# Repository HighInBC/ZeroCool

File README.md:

# ZeroCool
Zero cool is a Raspberry Pi Zero based portable bitcoin wallet printer.

This project is not ready for public consumption at this point.

The name of the project is a reference to one of the best/worst hacker movies ever made **Hackers**(1995).

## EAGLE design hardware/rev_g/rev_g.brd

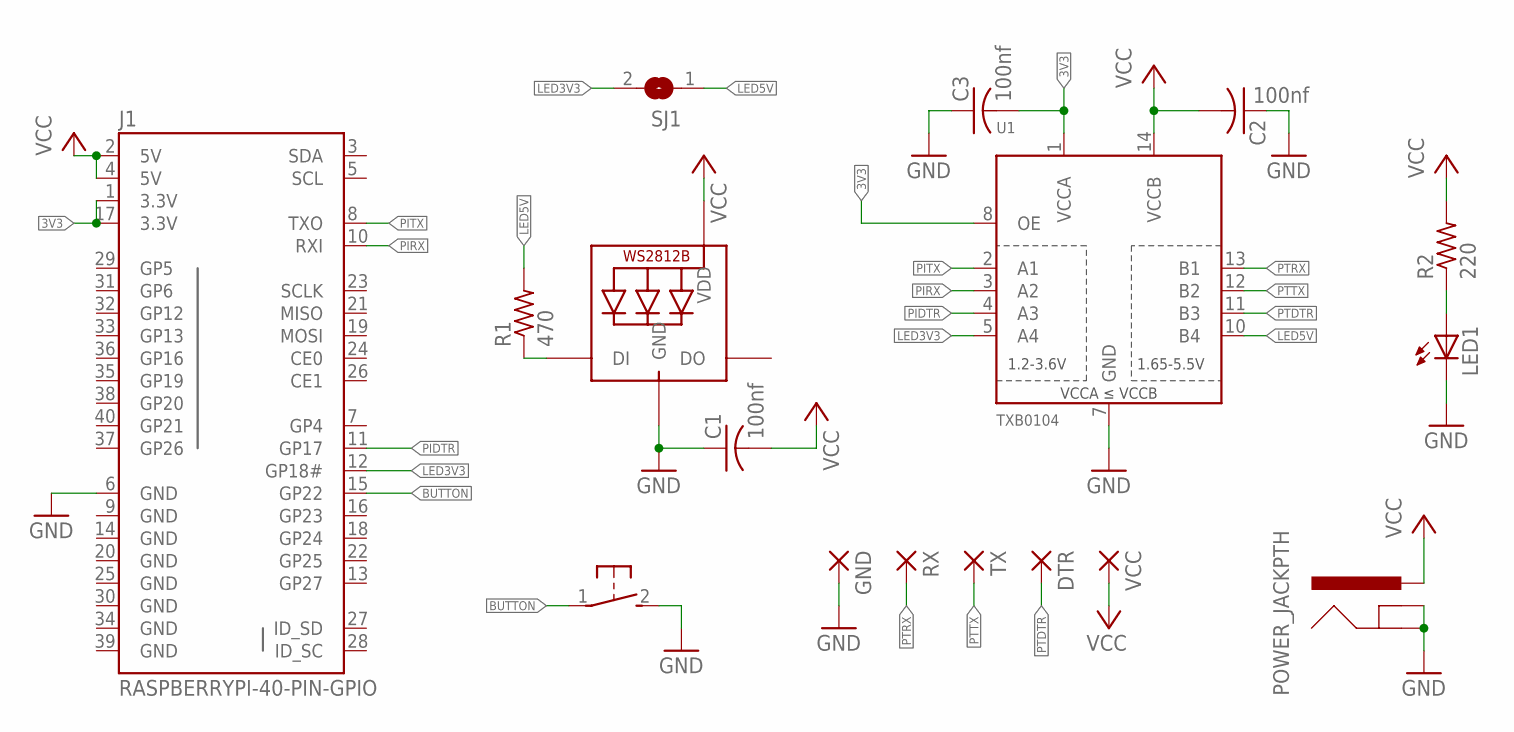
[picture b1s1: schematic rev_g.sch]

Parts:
C1, C2, C3: 100nf; C0805K
DTR: SMD5; SMD2,54-5,08
GND: SMD5; SMD2,54-5,08
J1: RASPBERRYPI-40-PIN-GPIO; 2X20-SHROUDED
J3: POWER_JACKPTH; POWER_JACK_PTH
LED1: LEDCHIPLED_0805; CHIPLED_0805
LED2: WS2812B5050; WS2812B
R1: 470; M0805
R2: 220; M0805
RX: SMD5; SMD2,54-5,08
S1: DTSM-3
SJ1: SJ
TX: SMD5; SMD2,54-5,08
U1: TXB0104; TSSOP14
VCC: SMD5; SMD2,54-5,08

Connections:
3V3: C3.2, J1.1 (3.3V), J1.17 (3.3V), U1.1 (VCCA), U1.8 (OE)
BUTTON: J1.15 (GP22), S1.1
GND: C1.1, C2.1, C3.1, GND.1, J1.6 (GND), J1.9 (GND), J1.14 (GND), J1.20 (GND), J1.25 (GND), J1.30 (GND), J1.34 (GND), J1.39 (GND), J3.GND, J3.GNDBREAK, LED1.C, LED2.3-GND (GND), S1.2, U1.7 (GND)
LED3V3: J1.12 (GP18#), SJ1.2, U1.5 (A4)
LED5V: R1.2, SJ1.1, U1.10 (B4)
unnamed: LED2.4-DIN (DI), R1.1
unnamed: LED1.A, R2.1
PIDTR: J1.11 (GP17), U1.4 (A3)
PIRX: J1.10 (RXI), U1.3 (A2)
PITX: J1.8 (TXO), U1.2 (A1)
PTDTR: DTR.1, U1.11 (B3)
PTRX: RX.1, U1.13 (B1)
PTTX: TX.1, U1.12 (B2)
VCC: C1.2, C2.2, J1.2 (5V), J1.4 (5V), J3.PWR, LED2.1-VDD (VDD), R2.2, U1.14 (VCCB), VCC.1

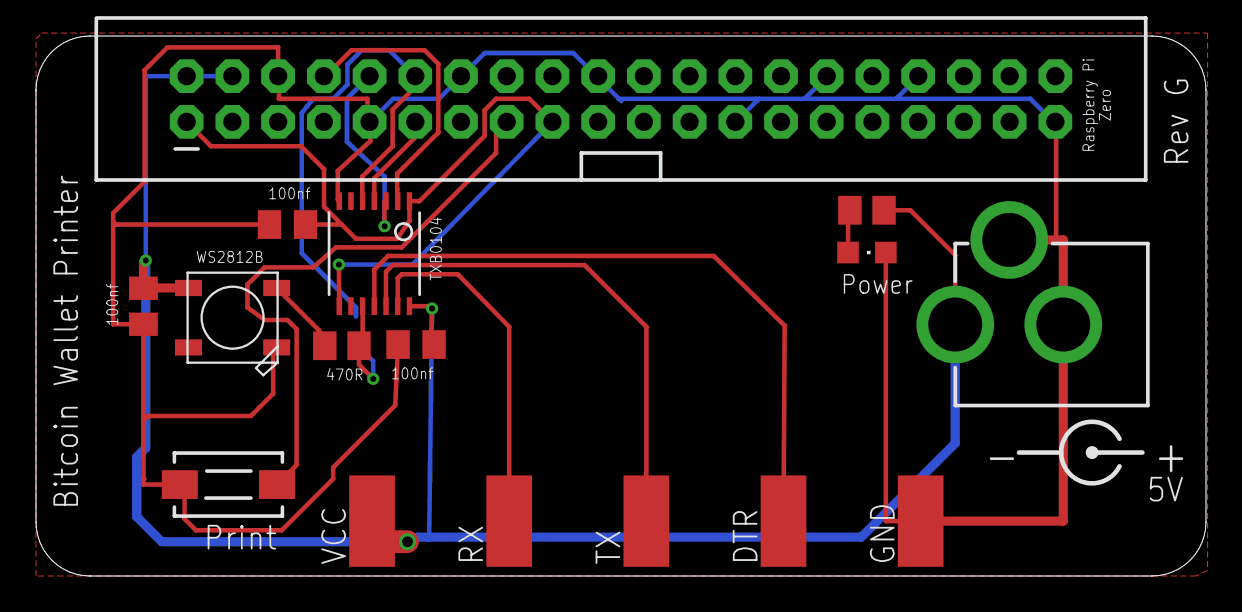
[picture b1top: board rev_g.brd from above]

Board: 2 copper layers, 65.0 x 30.0 mm, 17 parts (1 on the bottom side), 14 nets.

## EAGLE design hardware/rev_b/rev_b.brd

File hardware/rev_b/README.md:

Warning, this board revision has serious flaws including the barrel jack having the wrong polarity.
DO NOT USE

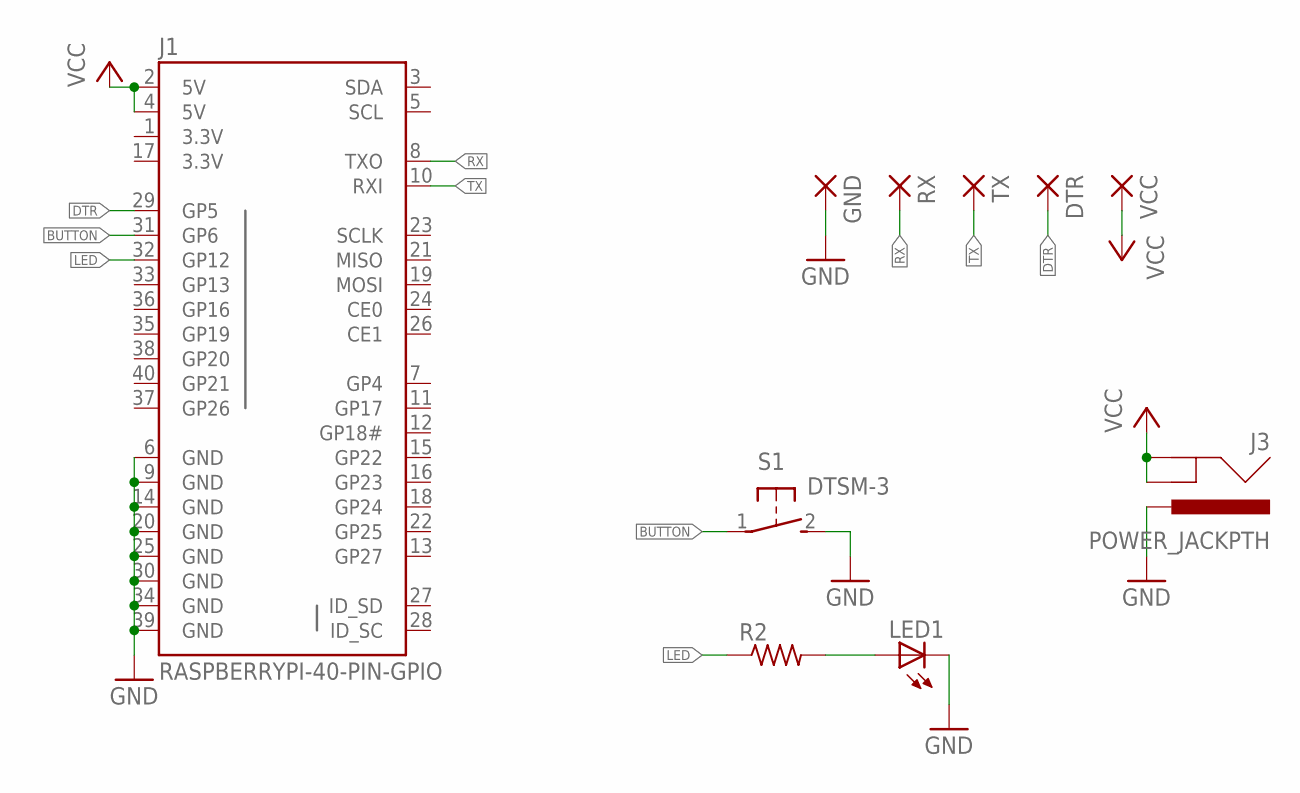
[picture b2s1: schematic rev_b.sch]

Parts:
DTR: SMD5; SMD2,54-5,08
GND: SMD5; SMD2,54-5,08
J1: RASPBERRYPI-40-PIN-GPIO; 2X20-SHROUDED
J3: POWER_JACKPTH; POWER_JACK_PTH
LED1: LEDSML0805; SML0805
R2: R-US_R0805; R0805
RX: SMD5; SMD2,54-5,08
S1: DTSM-3
TX: SMD5; SMD2,54-5,08
VCC: SMD5; SMD2,54-5,08

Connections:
3.3V: J1.1 (3.3V), J1.17 (3.3V)
BUTTON: J1.31 (GP6), S1.1
DTR: DTR.1, J1.29 (GP5)
GND: GND.1, J1.6 (GND), J1.9 (GND), J1.14 (GND), J1.20 (GND), J1.25 (GND), J1.30 (GND), J1.34 (GND), J1.39 (GND), J3.PWR, LED1.C, S1.2
LED: J1.32 (GP12), R2.1
unnamed: LED1.A, R2.2
RX: J1.8 (TXO), RX.1
TX: J1.10 (RXI), TX.1
VCC: J1.2 (5V), J1.4 (5V), J3.GND, J3.GNDBREAK, VCC.1

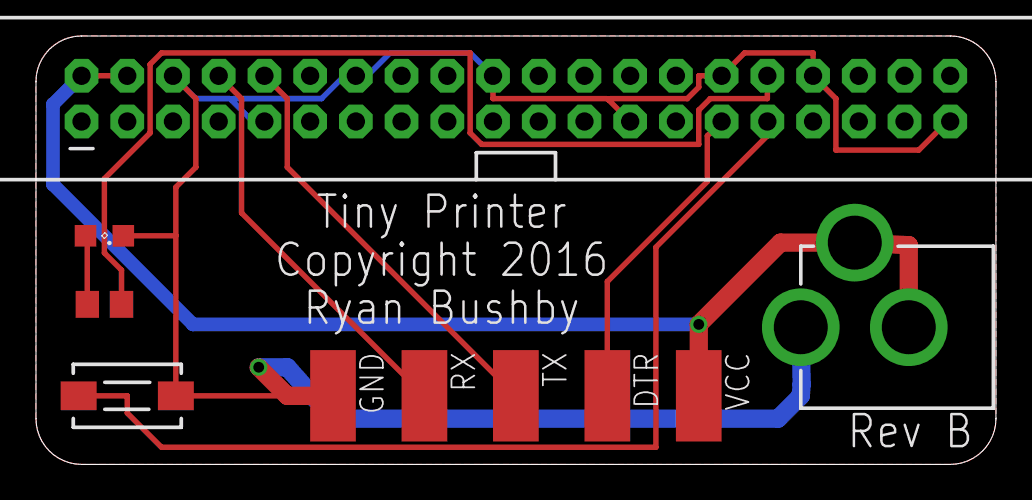
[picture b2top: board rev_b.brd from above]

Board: 2 copper layers, 53.3 x 23.8 mm, 10 parts (0 on the bottom side), 9 nets.

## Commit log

2016-07-30 Adding not about unreadiness
2016-07-30 best/worst hacker movie
2016-07-31 Initial version of software
2016-07-31 remove from base
2016-07-31 Early hardware revision
2016-07-31 more recent version
2016-08-05 license

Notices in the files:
hardware/rev_b/rev_b.brd:
Copyright 2016
hardware/rev_g/rev_g.brd:
Copyright Ryan Bushby
parts and their libraries:
SparkFun-Boards: Licensing: Creative Commons ShareAlike 4.0 International - https://creativecommons.org/licenses/by-sa/4.0
